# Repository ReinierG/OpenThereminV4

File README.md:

# OpenThereminV4
Open Source Theremin Instrument

Schematics, printed circuit board (PCB) design, bill of materials (BOM) and Arduino UNO compatible software for the OpenTheremin V4

### Open Source Theremin based on the Arduino Platform

OpenTheremin is an arduino based real Therein instrument. The legendary music instrument was invented by Leon Theremin back in 1920. The theremin is played with two antennas, one to control the pitch and one for volume. The electronic shield with two ports to connect those antennas comprises two heterodyne oscillators to measure the distance of the hand to the antenna when playing the instrument. The resulting signal is fed into a AtMega328P microcontroller. After linearization and filtering the circuit generates the instruments sound that is then played through a high quality digital analog audio converter on the board. The characteristics of the sound can be determined by a wave table on the arduino.

For more info on the open source project and on availability of ready made shield see:

http://www.gaudi.ch/OpenTheremin/

Modifications to the original project
-  4-layer pcb for improved emc performance (slightly more expensive)
-  1 layer for ground, 1 layer for power (5V and a few 3.3V traces)
-  improved audio noise performance
-  added ESD protection (antennas, USB, audio connector, touch button)
-  added quite a few decoupling and bulk capacitors
-  solved a lot of design rule errors
-  removed some BOM errors and wrong footprints (3.5 mm audio connector)
-  100% software compatible
-  migrated to KiCAD 9.0.4

### Installation
1. Open up the Arduino IDE
2. Open the File "Open_Theremin_V4.ino"
3. Selecting the correct usb port on Tools -> Serial Port
4. Select the correct arduino board from Tools -> Board
5. Upload the code by clicking on the upload button.

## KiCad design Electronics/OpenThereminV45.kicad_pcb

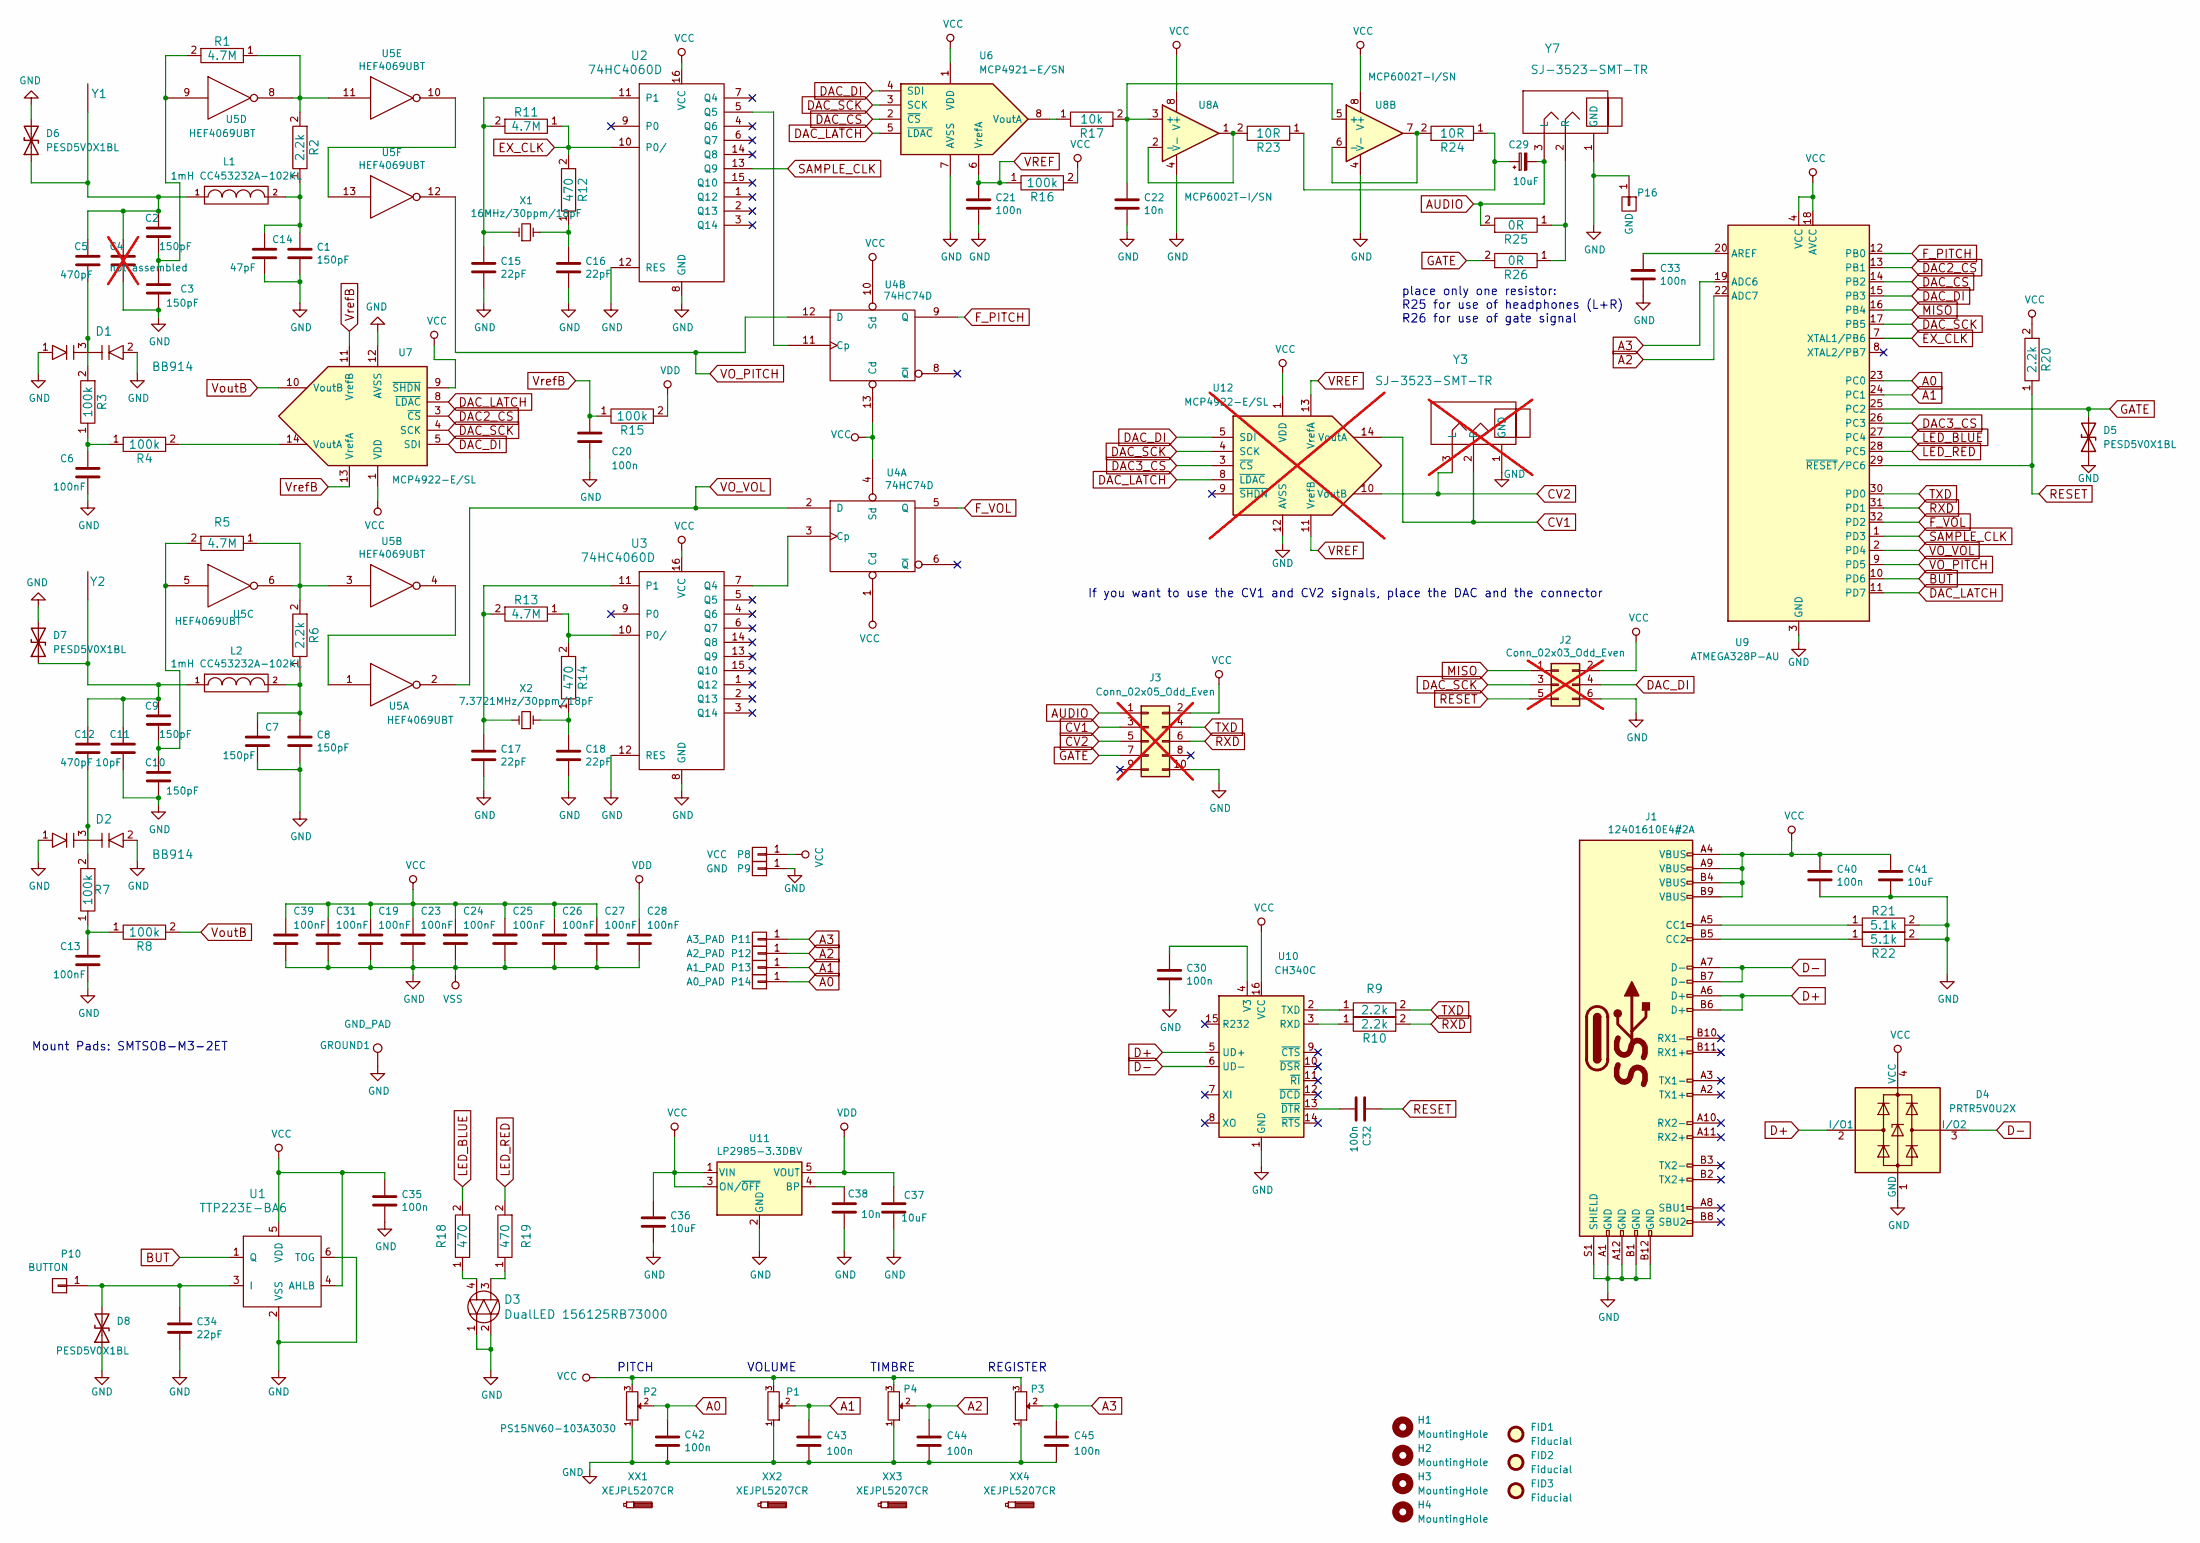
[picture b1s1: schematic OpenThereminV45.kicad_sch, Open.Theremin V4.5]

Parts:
C1, C2, C3, C7, C8, C9, C10: 150pF; C_0603_1608Metric
C4: not assembled; C_0603_1608Metric; not fitted
C5, C12: 470pF; C_0603_1608Metric
C6, C13, C19, C23, C24, C25, C26, C27, C28, C31, C39: 100nF; C_0603_1608Metric
C11: 10pF; C_0603_1608Metric
C14: 47pF; C_0603_1608Metric
C15, C16, C17, C18, C34: 22pF; C_0603_1608Metric
C20, C21, C30, C32, C33, C35, C40, C42, C43, C44, C45: 100n; C_0603_1608Metric
C22, C38: 10n; C_0603_1608Metric
C29, C36, C37, C41: 10uF; C_0603_1608Metric
D1, D2: BB914; SOT-23
D3: DualLED 156125RB73000; WL-SBRW
D4: PRTR5V0U2X; SOT-143
D5, D6, D7, D8: PESD5V0X1BL; D_SOD-882
FID1, FID2, FID3: Fiducial; Fiducial_1mm_Mask3mm
GROUND1: GND_PAD; GNDPad
H1, H2, H3, H4: MountingHole; MountingHole_3.2mm_M3
J1: 12401610E4#2A; USB_C_Receptacle_Amphenol_12401610E4-2A
J2: Conn_02x03_Odd_Even; Tag-Connect_TC2030-IDC-NL_2x03_P1.27mm_Vertical; not fitted
J3: Conn_02x05_Odd_Even; PinHeader_2x05_P1.27mm_Vertical_SMD; not fitted
L1, L2: 1mH CC453232A-102KL; COIL_T
P1, P2, P3, P4: PS15NV60-103A3030; PS15NV60
P8: VCC; SMD_Pinheader_1_OT_BLANK
P9, P16: GND; SMD_Pinheader_1_OT_BLANK
P10: BUTTON; SensorButton
P11: A3_PAD; SMD_Pinheader_1_OT_BLANK
P12: A2_PAD; SMD_Pinheader_1_OT_BLANK
P13: A1_PAD; SMD_Pinheader_1_OT_BLANK
P14: A0_PAD; SMD_Pinheader_1_OT_BLANK
R1, R5, R11, R13: 4.7M; R_0603_1608Metric
R2, R6, R9, R10, R20: 2.2k; R_0603_1608Metric
R3, R4, R7, R8, R15, R16: 100k; R_0603_1608Metric
R12, R14, R18, R19: 470; R_0603_1608Metric
R17: 10k; R_0603_1608Metric
R21, R22: 5.1k; R_0603_1608Metric
R23, R24: 10R; R_0603_1608Metric
R25, R26: 0R; R_0603_1608Metric
U1: TTP223E-BA6; SOT-23-6
U2, U3: 74HC4060D; SOIC-16_3.9x9.9mm_P1.27mm
U4: 74HC74D; SOIC-14_3.9x8.7mm_P1.27mm
U5: HEF4069UBT; SOIC-14_3.9x8.7mm_P1.27mm
U6: MCP4921-E/SN; SOIC-8_3.9x4.9mm_P1.27mm
U7: MCP4922-E/SL; SOIC-14_3.9x8.7mm_P1.27mm
U8: MCP6002T-I/SN; SOIC-8_3.9x4.9mm_P1.27mm
U9: ATMEGA328P-AU; TQFP-32_7x7mm_P0.8mm
U10: CH340C; SOIC-16_3.9x9.9mm_P1.27mm
U11: LP2985-3.3DBV; SOT-23-5
U12: MCP4922-E/SL; SOIC-14_3.9x8.7mm_P1.27mm; not fitted
X1: 16MHz/30ppm/18pF; Crystal_SMD_HC49-SD
X2: 7.3721MHz/30ppm/18pF; Crystal_SMD_HC49-SD
XX1, XX2, XX3, XX4: XEJPL5207CR
Y1, Y2: MountPad3; SMTSOB_M3
Y3: SJ-3523-SMT-TR; SJ-3502-SMT-TR; not fitted
Y7: SJ-3523-SMT-TR; SJ-3502-SMT-TR

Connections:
A0: C42.1, P2.2, P14.1, U9.23 (PC0)
A1: C43.1, P1.2, P13.1, U9.24 (PC1)
A2: C44.1, P4.2, P12.1, U9.22 (ADC7)
A3: C45.1, P3.2, P11.1, U9.19 (ADC6)
AUDIO: C29.2, J3.1, R25.2, Y7.3 (L)
BUT: U1.1 (Q), U9.10 (PD6)
CV1: J3.3, U12.14 (VoutA), Y3.2 (R)
CV2: J3.5, U12.10 (VoutB), Y3.3 (L)
D+: D4.2 (I/O1), J1.A6 (D+), J1.B6 (D+), U10.5 (UD+)
D-: D4.3 (I/O2), J1.A7 (D-), J1.B7 (D-), U10.6 (UD-)
DAC2_CS: U7.3 (~CS), U9.13 (PB1)
DAC3_CS: U9.26 (PC3), U12.3 (~CS)
DAC_CS: U6.2 (~CS), U9.14 (PB2)
DAC_DI: J2.4, U6.4 (SDI), U7.5 (SDI), U9.15 (PB3), U12.5 (SDI)
DAC_LATCH: U6.5 (~LDAC), U7.8 (~LDAC), U9.11 (PD7), U12.8 (~LDAC)
DAC_SCK: J2.3, U6.3 (SCK), U7.4 (SCK), U9.17 (PB5), U12.4 (SCK)
EX_CLK: R11.1, R12.2, U2.10 (P0/), U9.7 (XTAL1/PB6)
F_PITCH: U4.9 (Q), U9.12 (PB0)
F_VOL: U4.5 (Q), U9.32 (PD2)
GATE: D5.2 (A2), J3.7, R26.2, U9.25 (PC2)
GND: C1.2, C3.2, C4.2, C6.2, C7.2, C8.2, C10.2, C11.2, C13.2, C14.2, C15.2, C16.2, C17.2, C18.2, C19.2, C20.2, C21.2, C22.2, C23.2, C24.2, C25.2, C26.2, C27.2, C28.2, C30.2, C31.2, C33.2, C34.2, C35.2, C36.2, C37.2, C38.2, C39.2, C40.2, C41.2, C42.2, C43.2, C44.2, C45.2, D1.1, D1.2, D2.1, D2.2, D3.1, D3.2, D4.1 (GND), D5.1 (A1), D6.2 (A2), D7.2 (A2), D8.1 (A1), GROUND1.1, J1.A1 (GND), J1.A12 (GND), J1.B1 (GND), J1.B12 (GND), J1.S1 (SHIELD), J2.6, J3.10, P1.1, P2.1, P3.1, P4.1, P9.1, P16.1, R21.2, R22.2, U1.2 (VSS), U1.6 (TOG), U2.8 (GND), U2.12 (RES), U3.8 (GND), U3.12 (RES), U4.7 (GND), U5.7 (VSS), U6.7 (AVSS), U7.12 (AVSS), U8.4 (V-), U9.3 (GND), U9.5 (GND), U9.21 (GND), U10.1 (GND), U11.2 (GND), U12.12 (AVSS), Y3.1 (GND), Y7.1 (GND)
LED_BLUE: R18.2, U9.27 (PC4)
LED_RED: R19.2, U9.28 (PC5)
MISO: J2.1, U9.16 (PB4)
unnamed: C1.1, C14.1, L1.2, R2.1
unnamed: C2.2, C3.1, R1.2, U5.9
unnamed: C5.2, D1.3, R3.2
unnamed: C6.1, R3.1, R4.1
unnamed: C7.1, C8.1, L2.2, R6.1
unnamed: C9.2, C10.1, R5.2, U5.5
unnamed: C12.2, D2.3, R7.2
unnamed: C13.1, R7.1, R8.1
unnamed: C16.1, R12.1, X1.2
unnamed: C18.1, R14.1, X2.2
unnamed: C29.1, R23.1, R24.1
unnamed: D3.3, R19.1
unnamed: D3.4, R18.1
unnamed: C2.1, C4.1, C5.1, D6.1 (A1), L1.1, Y1.1
unnamed: C9.1, C11.1, C12.1, D7.1 (A1), L2.1, Y2.1
unnamed: C34.1, D8.2 (A2), P10.1, U1.3 (I)
unnamed: J1.A5 (CC1), R21.1
unnamed: J1.B5 (CC2), R22.1
unnamed: R1.1, R2.2, U5.8, U5.11
unnamed: R5.1, R6.2, U5.3, U5.6
unnamed: C15.1, R11.2, U2.11 (P1), X1.1
unnamed: U2.5 (Q5), U4.11 (Cp)
unnamed: R13.1, R14.2, U3.10 (P0/)
unnamed: C17.1, R13.2, U3.11 (P1), X2.1
unnamed: U3.7 (Q4), U4.3 (Cp)
unnamed: U5.1, U5.4
unnamed: U5.10, U5.13
unnamed: R17.1, U6.8 (VoutA)
unnamed: R4.2, U7.14 (VoutA)
unnamed: C22.1, R17.2, U8.3 (+), U8.5 (+)
unnamed: R23.2, U8.1, U8.2 (-)
unnamed: R24.2, U8.6 (-), U8.7
unnamed: C33.1, U9.20 (AREF)
unnamed: R10.1, U10.3 (RXD)
unnamed: R9.1, U10.2 (TXD)
unnamed: C30.1, U10.4 (V3)
unnamed: C32.2, U10.13 (~DTR)
unnamed: C38.1, U11.4 (BP)
unnamed: R25.1, R26.1, Y7.2 (R)
RESET: C32.1, J2.5, R20.1, U9.29 (~RESET/PC6)
RXD: J3.6, R10.2, U9.31 (PD1)
SAMPLE_CLK: U2.13 (Q9), U9.1 (PD3)
TXD: J3.4, R9.2, U9.30 (PD0)
VCC: C19.1, C23.1, C24.1, C25.1, C26.1, C27.1, C31.1, C35.1, C36.1, C39.1, C40.1, C41.1, D4.4 (VCC), J1.A4 (VBUS), J1.A9 (VBUS), J1.B4 (VBUS), J1.B9 (VBUS), J2.2, J3.2, P1.3, P2.3, P3.3, P4.3, P8.1, R16.2, R20.2, U1.4 (AHLB), U1.5 (VDD), U2.16 (VCC), U3.16 (VCC), U4.1 (Cd), U4.4 (Sd), U4.10 (Sd), U4.13 (Cd), U4.14 (VCC), U6.1 (VDD), U7.1 (VDD), U7.9 (~SHDN), U8.8 (V+), U9.4 (VCC), U9.6 (VCC), U9.18 (AVCC), U10.16 (VCC), U11.1 (VIN), U11.3 (ON/~OFF), U12.1 (VDD)
VDD: C28.1, C37.1, R15.2, U5.14 (VDD), U11.5 (VOUT)
VO_PITCH: U4.12 (D), U5.12, U9.9 (PD5)
VO_VOL: U4.2 (D), U5.2, U9.2 (PD4)
VREF: C21.1, R16.1, U6.6 (VrefA), U12.11 (VrefB), U12.13 (VrefA)
VoutB: R8.2, U7.10 (VoutB)
VrefB: C20.1, R15.1, U7.11 (VrefB), U7.13 (VrefA)

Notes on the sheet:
REGISTER
If you want to use the CV1 and CV2 signals, place the DAC and the connector
VOLUME
TIMBRE
PITCH
Mount Pads: SMTSOB-M3-2ET
place only one resistor: R25 for use of headphones (L+R) R26 for use of gate signal

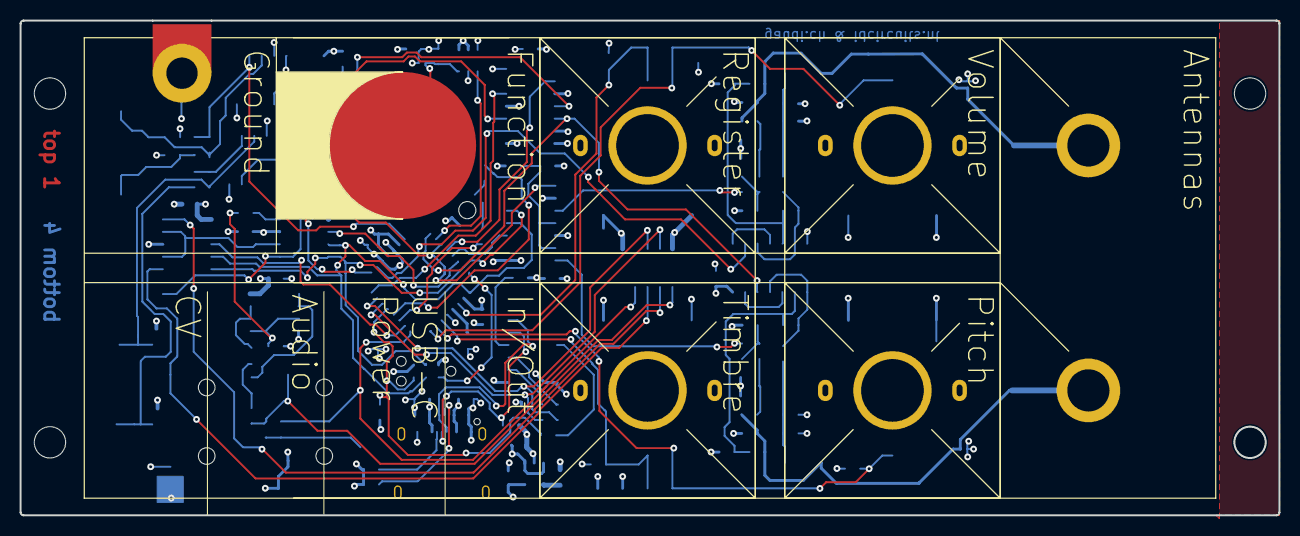
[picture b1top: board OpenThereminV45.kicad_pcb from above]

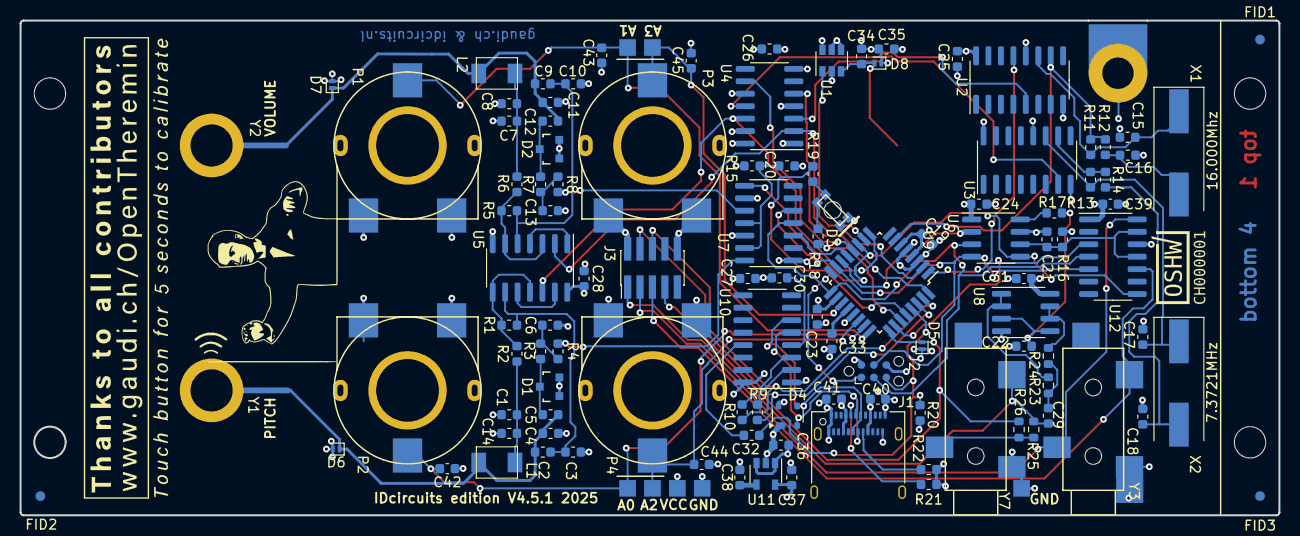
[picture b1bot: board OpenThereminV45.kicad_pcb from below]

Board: 4 copper layers, 128.5 x 50.5 mm, 122 parts (114 on the bottom side), 74 nets.

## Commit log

2025-08-26 changed to 4-layer and added esd protection and bypass caps
    not final yet, audio connector has wrong footprint
2025-08-26 added gitignore
2025-08-27 Added some text; moved some reference descriptors; pcb layer identification
2025-09-01 4-layer version; 3D updates and more
